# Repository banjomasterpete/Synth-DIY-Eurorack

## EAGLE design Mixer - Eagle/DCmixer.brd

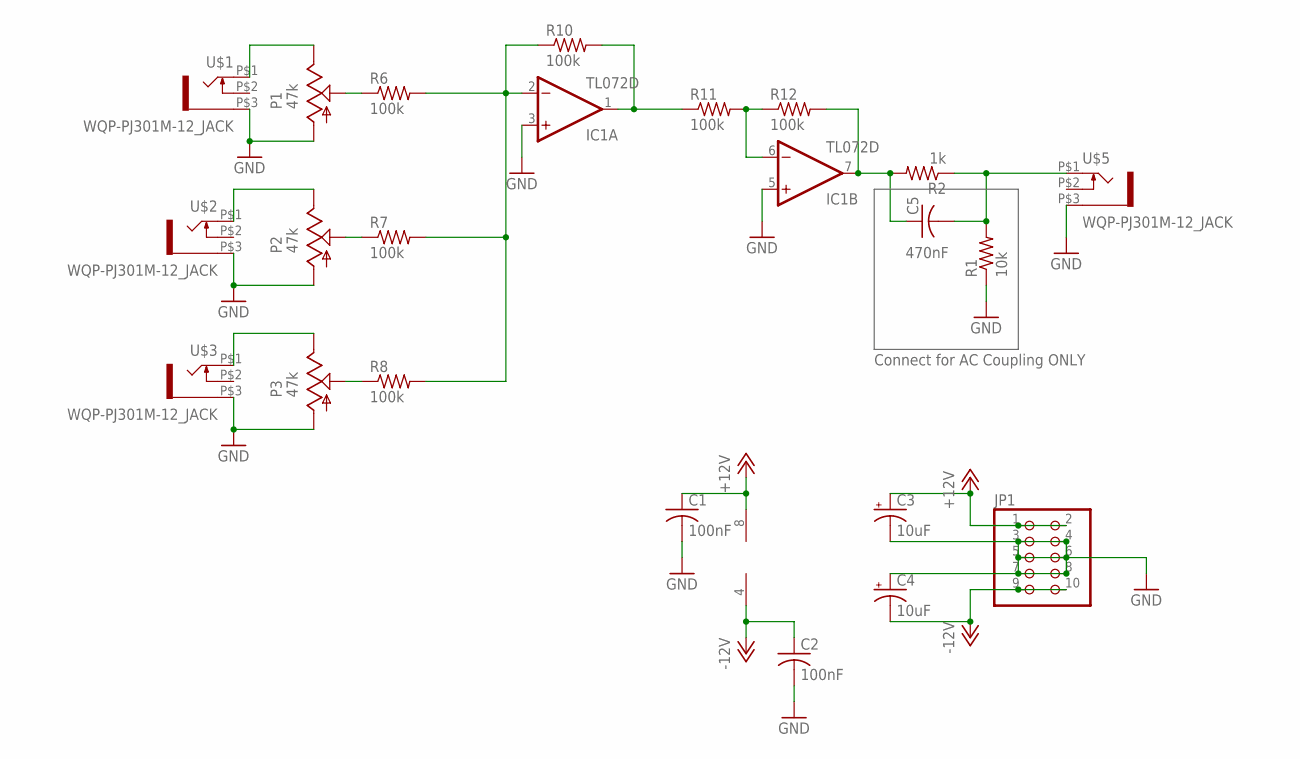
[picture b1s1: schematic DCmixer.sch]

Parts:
C1, C2: 100nF; C0603K
C3, C4: 10uF; E2-5
C5: 470nF; C0603K
IC1: TL072D; SO08
JP1: PINHD-2X5; 2X05
P1, P2, P3: 47k; EVUF
R1: 10k; R0603
R2: 1k; R0603
R6, R7, R8, R10, R11, R12: 100k; R0603
U$1, U$2, U$3, U$5: WQP-PJ301M-12_JACK

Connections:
+12V: C1.1, C3.+, IC1.8 (V+), JP1.1, JP1.2
-12V: C2.1, C4.-, IC1.4 (V-), JP1.9, JP1.10
GND: C1.2, C2.2, C3.-, C4.+, IC1.3 (+IN), IC1.5 (+IN), JP1.3, JP1.4, JP1.5, JP1.6, JP1.7, JP1.8, P1.1 (A), P2.1 (A), P3.1 (A), R1.1, U$1.P$3 (1), U$2.P$3 (1), U$3.P$3 (1), U$5.P$3 (1)
unnamed: P1.3 (E), U$1.P$1 (2)
unnamed: P2.3 (E), U$2.P$1 (2)
unnamed: P3.3 (E), U$3.P$1 (2)
unnamed: P3.2 (S), R8.1
unnamed: P2.2 (S), R7.1
unnamed: P1.2 (S), R6.1
unnamed: IC1.2 (-IN), R6.2, R7.2, R8.2, R10.1
unnamed: C5.2, R1.2, R2.1, U$5.P$1 (2)
unnamed: IC1.1 (OUT), R10.2, R11.1
unnamed: IC1.6 (-IN), R11.2, R12.1
unnamed: C5.1, IC1.7 (OUT), R2.2, R12.2

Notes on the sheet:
Connect for AC Coupling ONLY

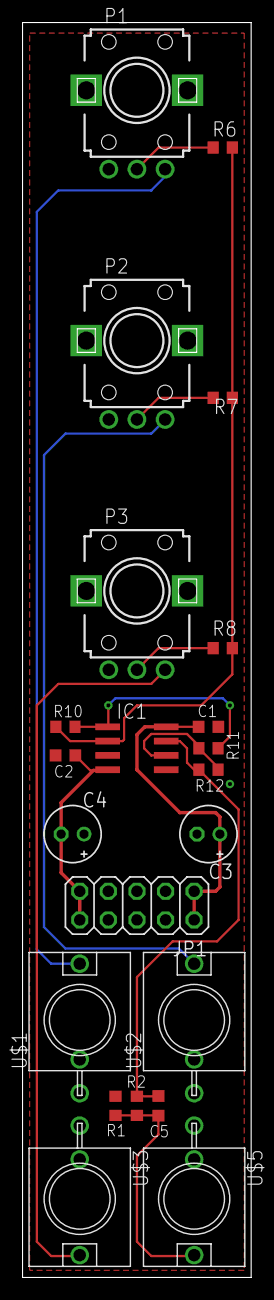
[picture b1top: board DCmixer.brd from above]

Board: 2 copper layers, 20.3 x 111.4 mm, 22 parts (0 on the bottom side), 14 nets.

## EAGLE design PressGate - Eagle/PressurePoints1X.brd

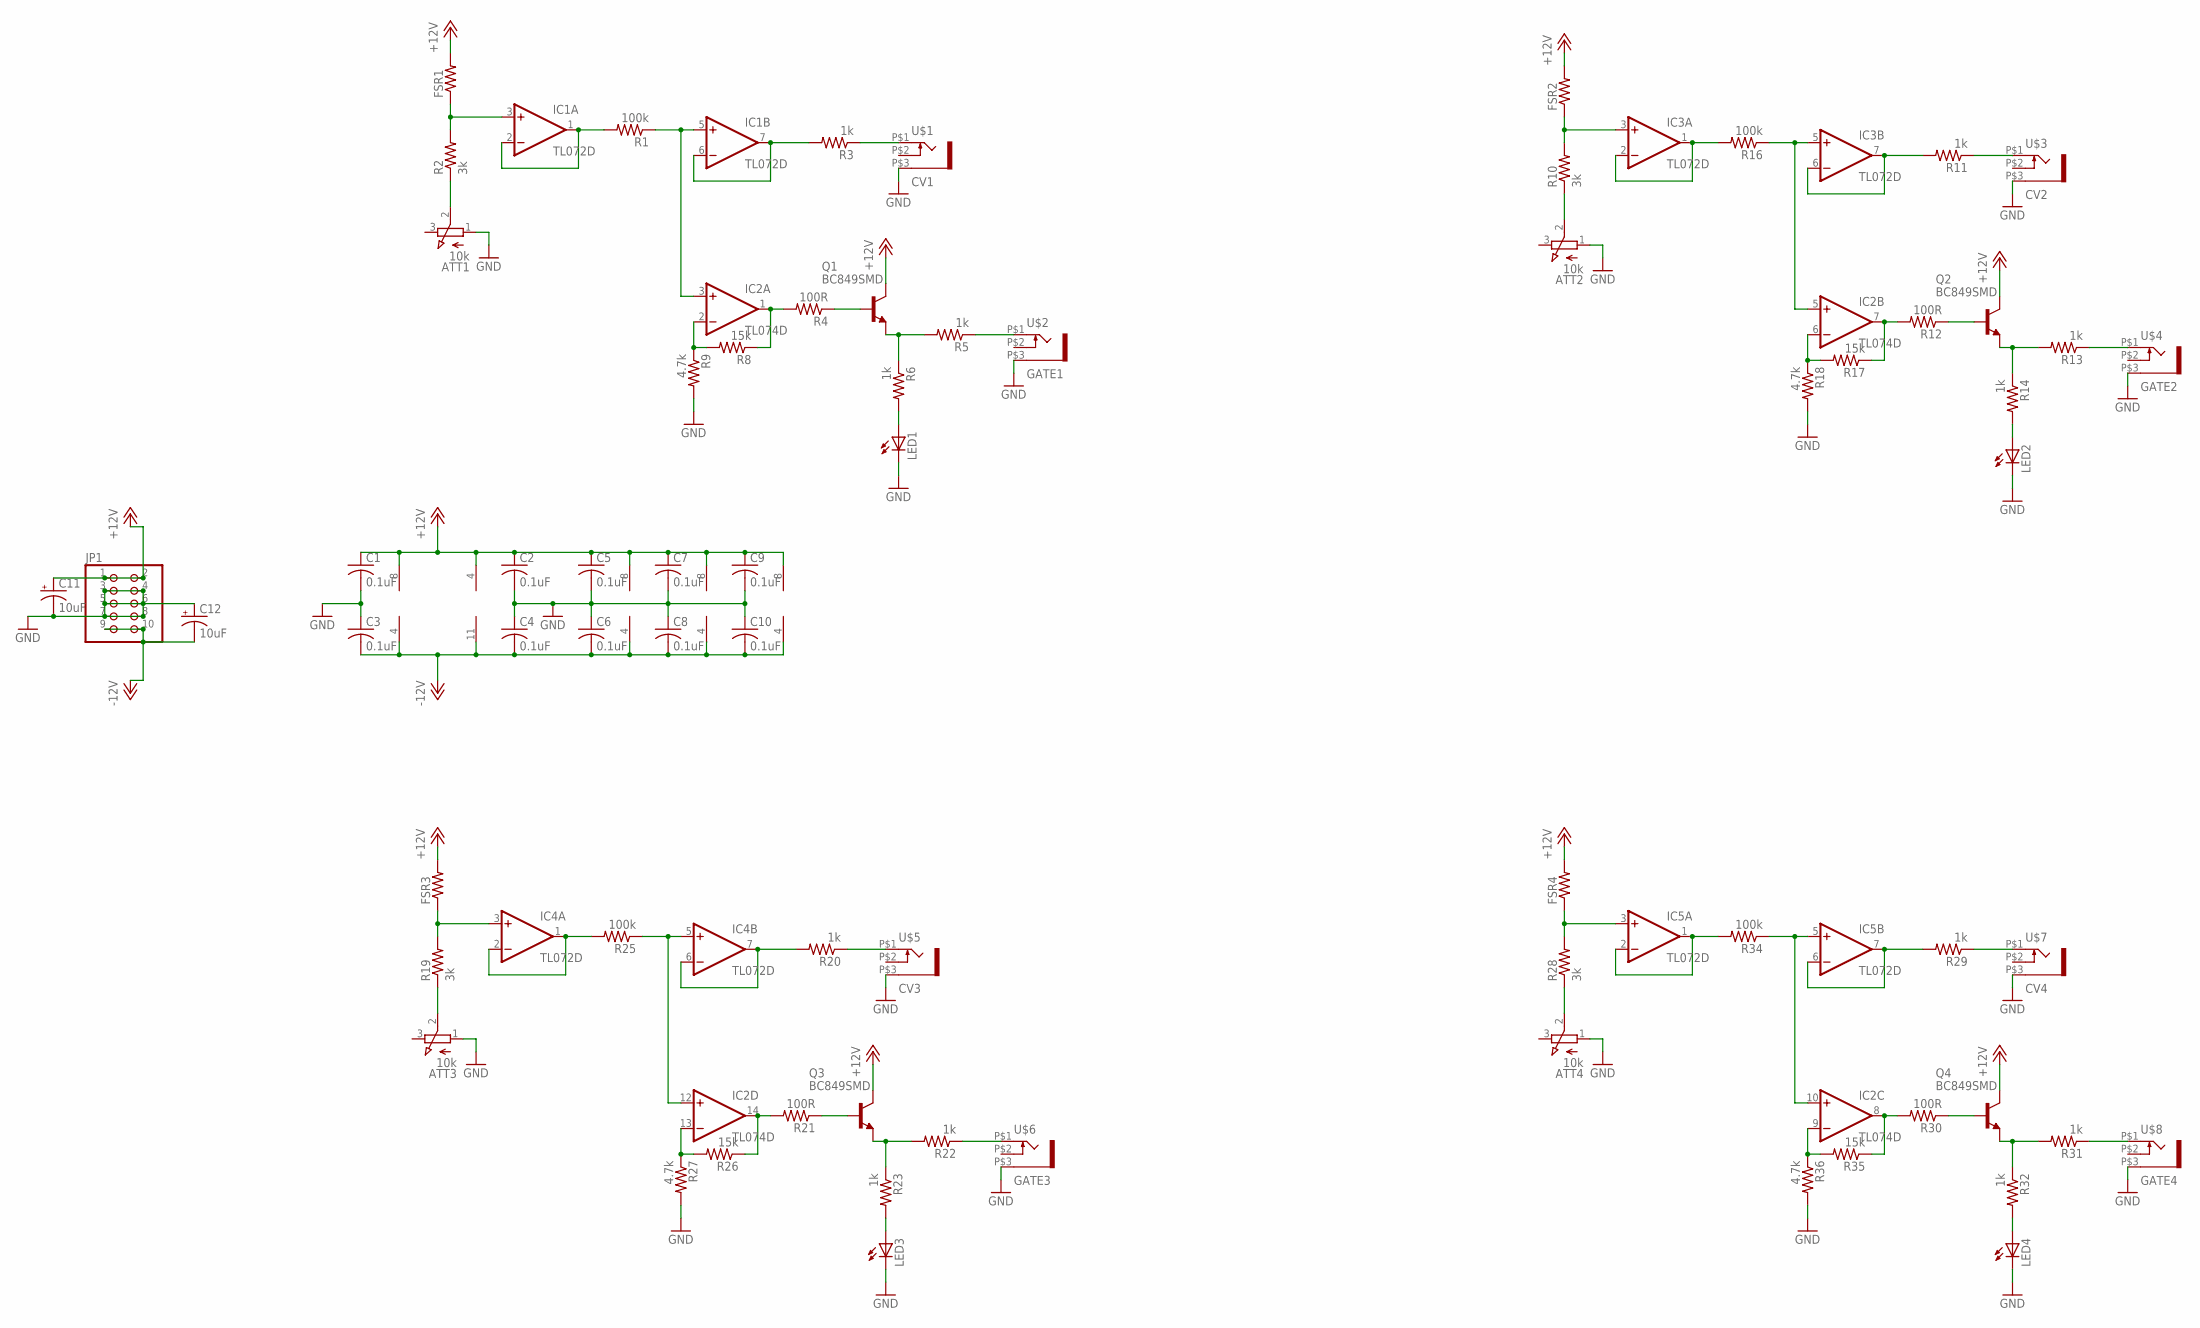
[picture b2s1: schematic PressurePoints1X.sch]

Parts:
ATT1, ATT2, ATT3, ATT4: 10k; EVUFXJ
C1, C2, C3, C4, C5, C6, C7, C8, C9, C10: 0.1uF; C0603
C11, C12: 10uF; E2-5
FSR1, FSR2, FSR3, FSR4: R-US_0207/2V; 0207/2V
IC1, IC3, IC4, IC5: TL072D; SO08
IC2: TL074D; SO14
JP1: PINHD-2X5; 2X05
LED1, LED2, LED3, LED4: LED3MM
Q1, Q2, Q3, Q4: BC849SMD; SOT23-BEC
R1, R16, R25, R34: 100k; R0603
R2, R10, R19, R28: 3k; R0603
R3, R5, R6, R11, R13, R14, R20, R22, R23, R29, R31, R32: 1k; R0603
R4, R12, R21, R30: 100R; R0603
R8, R17, R26, R35: 15k; R0603
R9, R18, R27, R36: 4.7k; R0603
U$1: CV1; WQP-PJ301M-12_JACK
U$2: GATE1; WQP-PJ301M-12_JACK
U$3: CV2; WQP-PJ301M-12_JACK
U$4: GATE2; WQP-PJ301M-12_JACK
U$5: CV3; WQP-PJ301M-12_JACK
U$6: GATE3; WQP-PJ301M-12_JACK
U$7: CV4; WQP-PJ301M-12_JACK
U$8: GATE4; WQP-PJ301M-12_JACK

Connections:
+12V: C1.1, C2.1, C5.1, C7.1, C9.1, C11.+, FSR1.2, FSR2.2, FSR3.2, FSR4.2, IC1.8 (V+), IC2.4 (V+), IC3.8 (V+), IC4.8 (V+), IC5.8 (V+), JP1.1, JP1.2, Q1.C, Q2.C, Q3.C, Q4.C
-12V: C3.2, C4.2, C6.2, C8.2, C10.2, C12.-, IC1.4 (V-), IC2.11 (V-), IC3.4 (V-), IC4.4 (V-), IC5.4 (V-), JP1.9, JP1.10
GND: ATT1.1 (A), ATT2.1 (A), ATT3.1 (A), ATT4.1 (A), C1.2, C2.2, C3.1, C4.1, C5.2, C6.1, C7.2, C8.1, C9.2, C10.1, C11.-, C12.+, JP1.3, JP1.4, JP1.5, JP1.6, JP1.7, JP1.8, LED1.K (C), LED2.K (C), LED3.K (C), LED4.K (C), R9.2, R18.2, R27.2, R36.2, U$1.P$3 (1), U$2.P$3 (1), U$3.P$3 (1), U$4.P$3 (1), U$5.P$3 (1), U$6.P$3 (1), U$7.P$3 (1), U$8.P$3 (1)
unnamed: FSR1.1, IC1.3 (+IN), R2.2
unnamed: ATT1.2 (S), R2.1
unnamed: IC1.5 (+IN), IC2.3 (+IN), R1.1
unnamed: IC1.6 (-IN), IC1.7 (OUT), R3.2
unnamed: R3.1, U$1.P$1 (2)
unnamed: Q1.E, R5.2, R6.1
unnamed: IC2.1 (OUT), R4.2, R8.1
unnamed: Q1.B, R4.1
unnamed: LED1.A, R6.2
unnamed: R5.1, U$2.P$1 (2)
unnamed: IC1.1 (OUT), IC1.2 (-IN), R1.2
unnamed: IC2.2 (-IN), R8.2, R9.1
unnamed: FSR2.1, IC3.3 (+IN), R10.2
unnamed: IC2.5 (+IN), IC3.5 (+IN), R16.1
unnamed: IC3.6 (-IN), IC3.7 (OUT), R11.2
unnamed: R11.1, U$3.P$1 (2)
unnamed: IC2.7 (OUT), R12.2, R17.1
unnamed: Q2.B, R12.1
unnamed: LED2.A, R14.2
unnamed: Q2.E, R13.2, R14.1
unnamed: R13.1, U$4.P$1 (2)
unnamed: ATT2.2 (S), R10.1
unnamed: IC3.1 (OUT), IC3.2 (-IN), R16.2
unnamed: IC2.6 (-IN), R17.2, R18.1
unnamed: FSR3.1, IC4.3 (+IN), R19.2
unnamed: IC2.12 (+IN), IC4.5 (+IN), R25.1
unnamed: IC4.6 (-IN), IC4.7 (OUT), R20.2
unnamed: R20.1, U$5.P$1 (2)
unnamed: IC2.14 (OUT), R21.2, R26.1
unnamed: Q3.B, R21.1
unnamed: LED3.A, R23.2
unnamed: Q3.E, R22.2, R23.1
unnamed: R22.1, U$6.P$1 (2)
unnamed: ATT3.2 (S), R19.1
unnamed: IC4.1 (OUT), IC4.2 (-IN), R25.2
unnamed: IC2.13 (-IN), R26.2, R27.1
unnamed: FSR4.1, IC5.3 (+IN), R28.2
unnamed: IC2.10 (+IN), IC5.5 (+IN), R34.1
unnamed: IC5.6 (-IN), IC5.7 (OUT), R29.2
unnamed: R29.1, U$7.P$1 (2)
unnamed: IC2.8 (OUT), R30.2, R35.1
unnamed: Q4.B, R30.1
unnamed: LED4.A, R32.2
unnamed: Q4.E, R31.2, R32.1
unnamed: R31.1, U$8.P$1 (2)
unnamed: ATT4.2 (S), R28.1
unnamed: IC5.1 (OUT), IC5.2 (-IN), R34.2
unnamed: IC2.9 (-IN), R35.2, R36.1

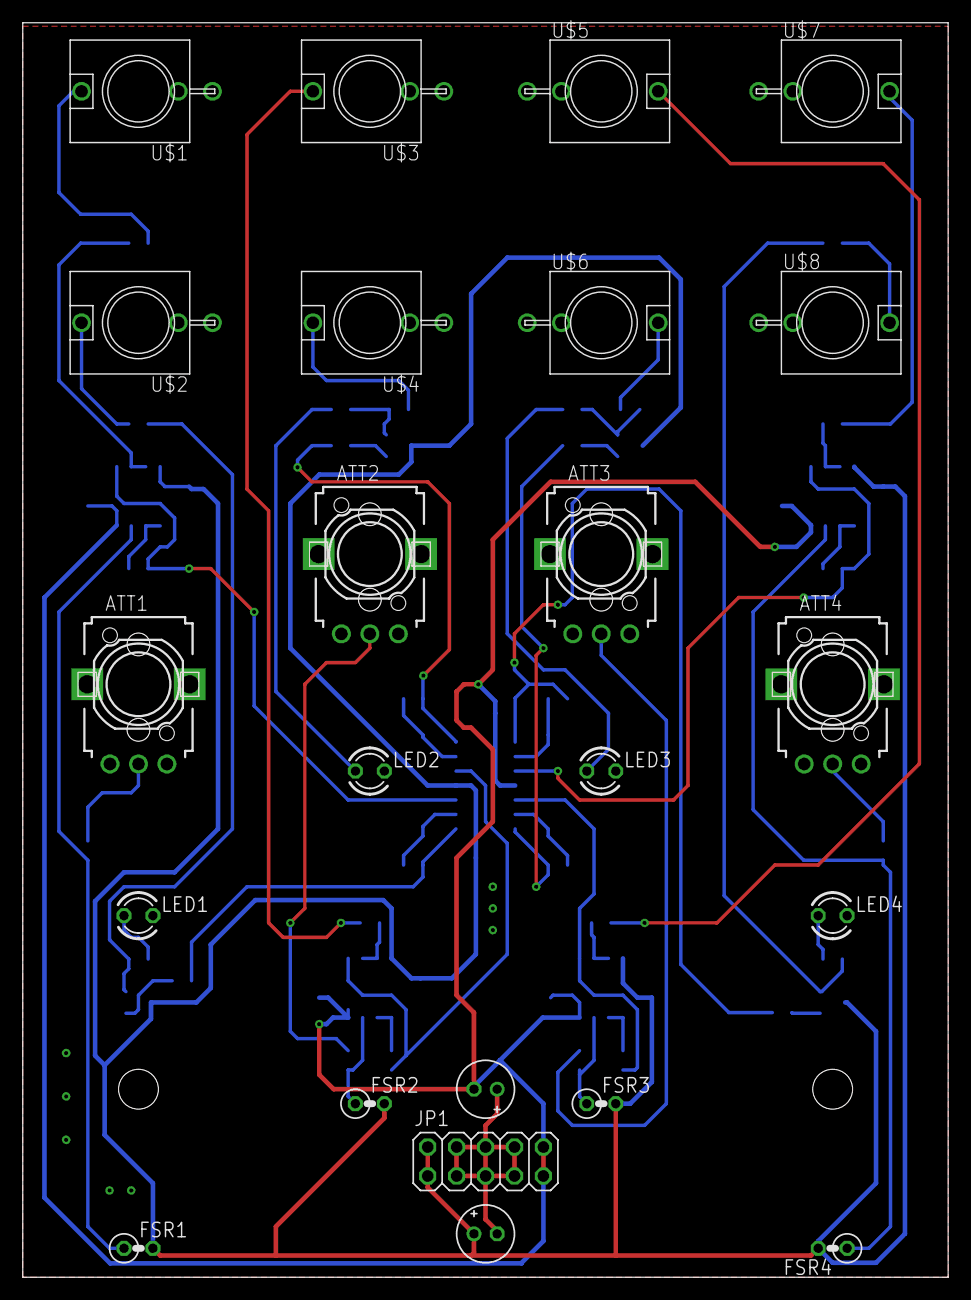
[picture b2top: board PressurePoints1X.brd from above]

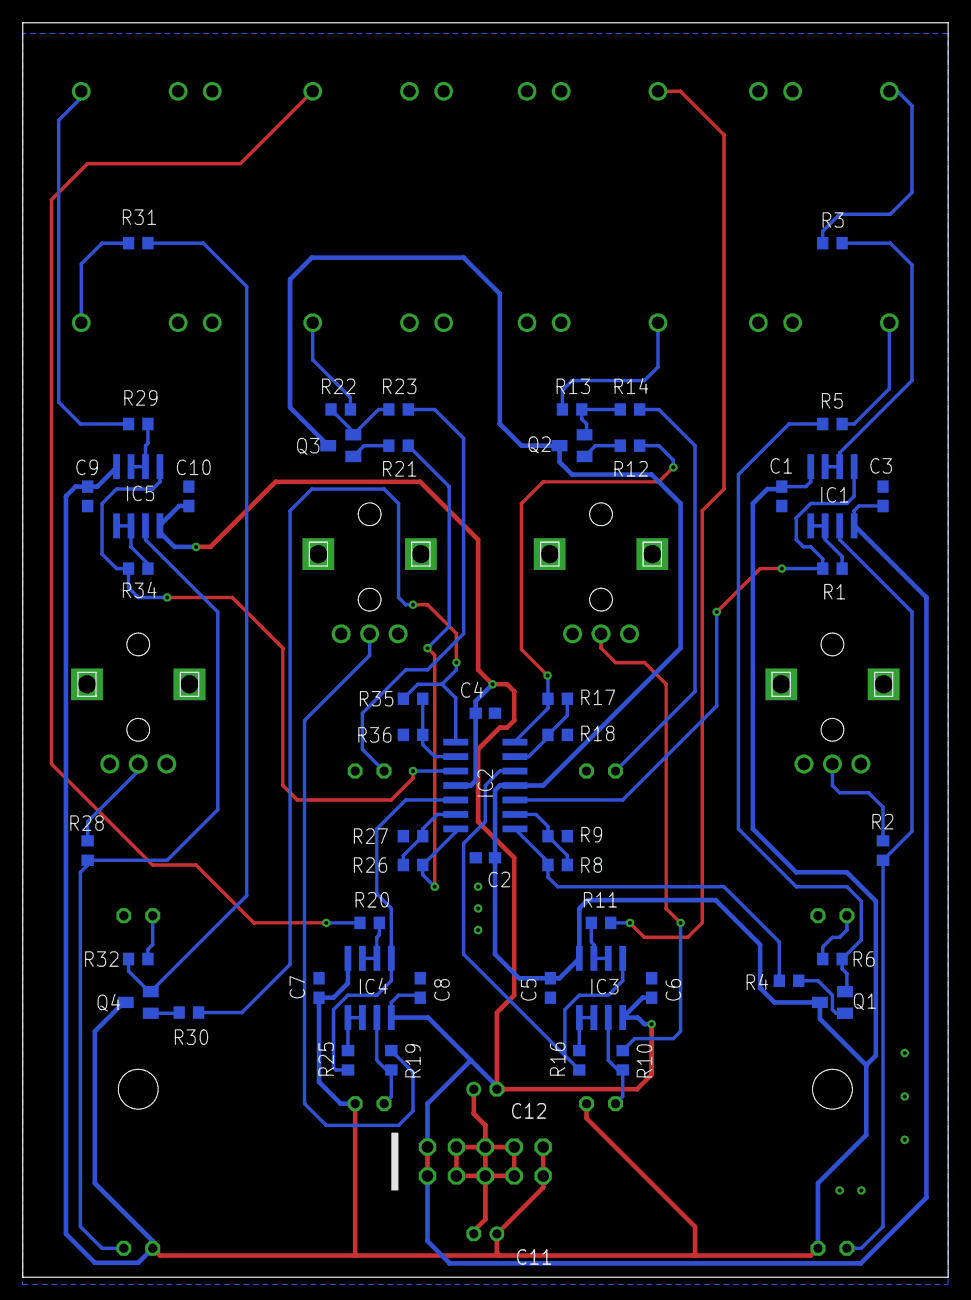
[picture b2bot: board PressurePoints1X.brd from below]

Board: 2 copper layers, 81.3 x 110.2 mm, 74 parts (51 on the bottom side), 51 nets.

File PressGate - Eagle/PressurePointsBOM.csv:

"Qty";"Value";"Device";"Package";"Parts";"Description";"SPICEPREFIX";
"4";"";"LED3MM";"LED3MM";"LED1, LED2, LED3, LED4";"LED";"";
"1";"";"PINHD-2X5";"2X05";"JP1";"PIN HEADER";"";
"4";"";"R-US_0207/2V";"0207/2V";"FSR1, FSR2, FSR3, FSR4";"RESISTOR, American symbol";"R";
"10";"0.1uF";"C-USC0603";"C0603";"C1, C2, C3, C4, C5, C6, C7, C8, C9, C10";"CAPACITOR, American symbol";"C";
"4";"100R";"R-US_R0603";"R0603";"R4, R12, R21, R30";"RESISTOR, American symbol";"R";
"4";"100k";"R-US_R0603";"R0603";"R1, R16, R25, R34";"RESISTOR, American symbol";"R";
"4";"10k";"EVUF2J";"EVUFXJ";"ATT1, ATT2, ATT3, ATT4";"9 mm Square Rotary Potentiometers";"";
"2";"10uF";"CPOL-USE2-5";"E2-5";"C11, C12";"POLARIZED CAPACITOR, American symbol";"C";
"4";"15k";"R-US_R0603";"R0603";"R8, R17, R26, R35";"RESISTOR, American symbol";"R";
"12";"1k";"R-US_R0603";"R0603";"R3, R5, R6, R11, R13, R14, R20, R22, R23, R29, R31, R32";"RESISTOR, American symbol";"R";
"4";"3k";"R-US_R0603";"R0603";"R2, R10, R19, R28";"RESISTOR, American symbol";"R";
"4";"4.7k";"R-US_R0603";"R0603";"R9, R18, R27, R36";"RESISTOR, American symbol";"R";
"4";"BC849SMD";"BC849SMD";"SOT23-BEC";"Q1, Q2, Q3, Q4";"NPN Transistor";"";
"1";"CV1";"WQP-PJ301M-12_JACK";"WQP-PJ301M-12_JACK";"U$1";"";"";
"1";"CV2";"WQP-PJ301M-12_JACK";"WQP-PJ301M-12_JACK";"U$3";"";"";
"1";"CV3";"WQP-PJ301M-12_JACK";"WQP-PJ301M-12_JACK";"U$5";"";"";
"1";"CV4";"WQP-PJ301M-12_JACK";"WQP-PJ301M-12_JACK";"U$7";"";"";
"1";"GATE1";"WQP-PJ301M-12_JACK";"WQP-PJ301M-12_JACK";"U$2";"";"";
"1";"GATE2";"WQP-PJ301M-12_JACK";"WQP-PJ301M-12_JACK";"U$4";"";"";
"1";"GATE3";"WQP-PJ301M-12_JACK";"WQP-PJ301M-12_JACK";"U$6";"";"";
"1";"GATE4";"WQP-PJ301M-12_JACK";"WQP-PJ301M-12_JACK";"U$8";"";"";
"4";"TL072D";"TL072D";"SO08";"IC1, IC3, IC4, IC5";"OP AMP";"";
"1";"TL074D";"TL074D";"SO14";"IC2";"OP AMP";"";

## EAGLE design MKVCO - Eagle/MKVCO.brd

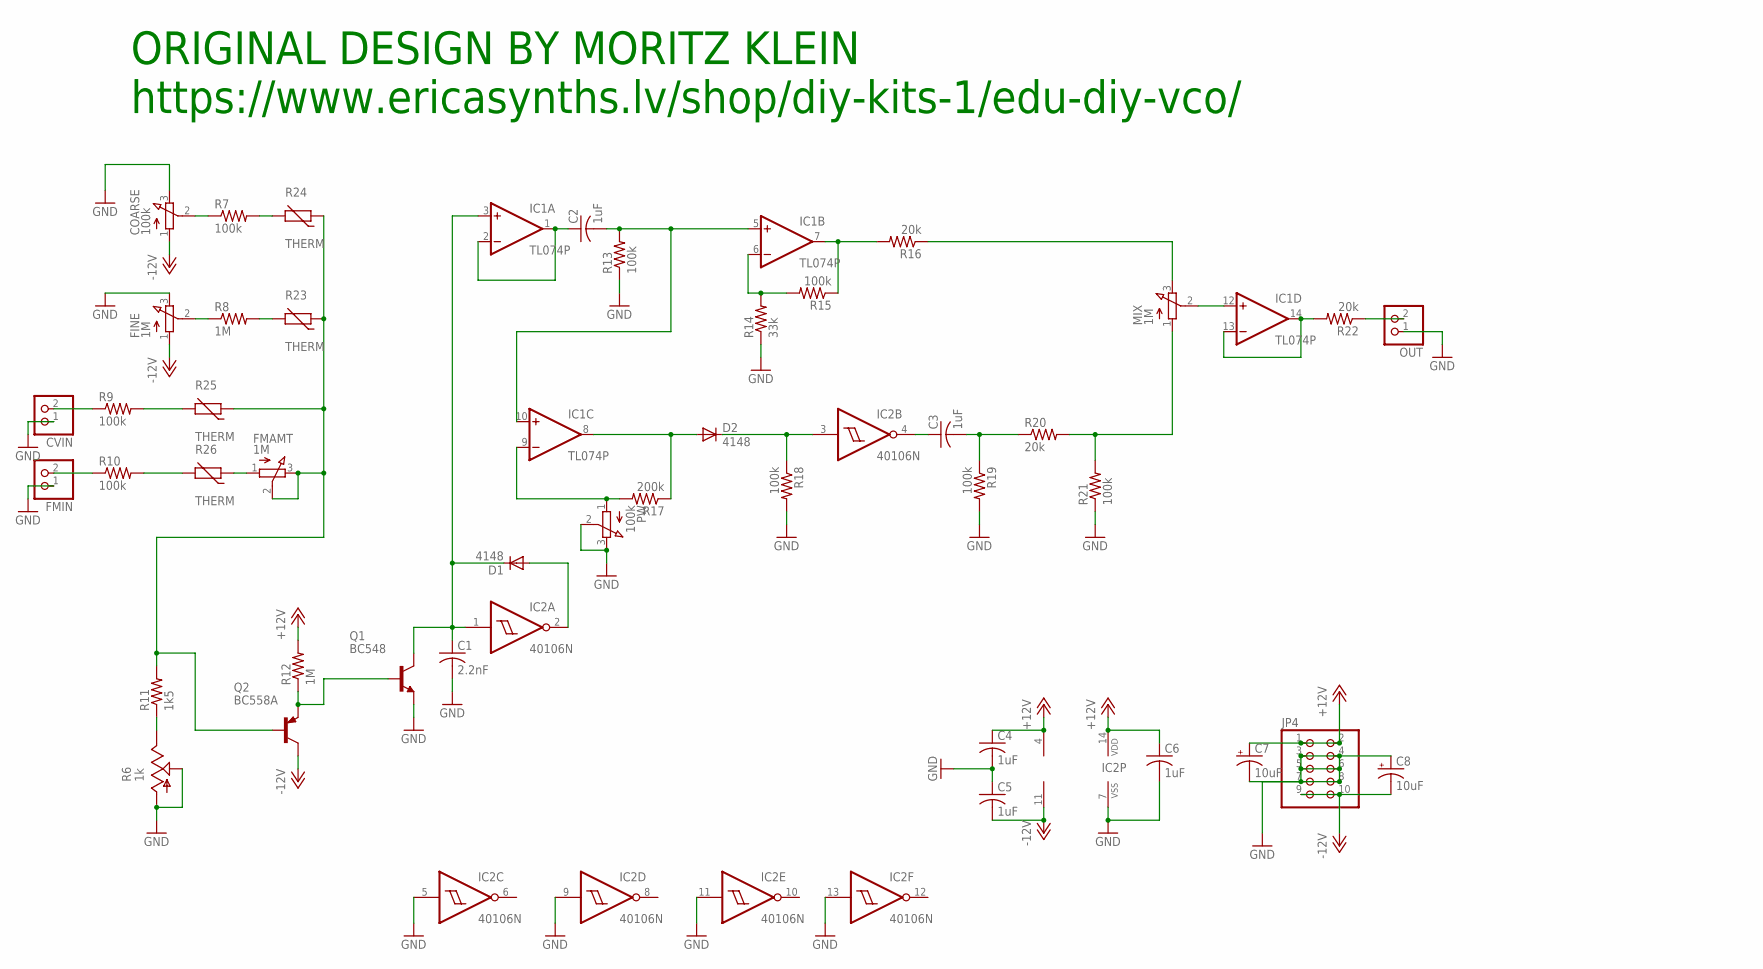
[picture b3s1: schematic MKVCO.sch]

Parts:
C1: 2.2nF; C050-025X075
C2, C3: 1uF; C050-025X075
C4, C5, C6: 1uF; C050-024X044
C7, C8: 10uF; E1,8-4
COARSE: 100k; 3RP/1610N
CVIN: PINHD-1X2; 1X02
D1, D2: 4148; DO35-7
FINE: 1M; 3RP/1610N
FMAMT: 1M; 3RP/1610N
FMIN: PINHD-1X2; 1X02
IC1: TL074P; DIL14
IC2: 40106N; DIL14
JP4: PINHD-2X5; 2X05
MIX: 1M; 3RP/1610N
OUT: PINHD-1X2; 1X02
PW: 100k; 3RP/1610N
Q1: BC548; TO92-EBC
Q2: BC558A; TO92-EBC
R6: 1k; B64Y
R7, R9, R10, R13, R15, R18, R19, R21: 100k; 0207/10
R8, R12: 1M; 0207/10
R11: 1k5; 0207/10
R14: 33k; 0207/10
R16, R20, R22: 20k; 0207/10
R17: 200k; 0207/10
R23, R24, R25, R26: THERM; RS-2,5

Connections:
+12V: C4.1, C6.1, C7.+, IC1.4 (V+), IC2.14 (VDD), JP4.1, JP4.2, R12.2
-12V: C5.2, C8.-, COARSE.1 (A), FINE.1 (A), IC1.11 (V-), JP4.9, JP4.10, Q2.C
GND: C1.2, C4.2, C5.1, C6.2, C7.-, C8.+, COARSE.3 (E), CVIN.1, FINE.3 (E), FMIN.1, IC2.5 (I), IC2.7 (VSS), IC2.9 (I), IC2.11 (I), IC2.13 (I), JP4.3, JP4.4, JP4.5, JP4.6, JP4.7, JP4.8, OUT.1, PW.2 (S), PW.3 (E), Q1.E, R6.A, R6.S, R13.1, R14.1, R18.2, R19.2, R21.1
unnamed: COARSE.2 (S), R7.1
unnamed: FINE.2 (S), R8.1
unnamed: CVIN.2, R9.1
unnamed: R9.2, R25.2
unnamed: FMAMT.2 (S), FMAMT.3 (E), Q2.B, R11.2, R23.1, R24.1, R25.1
unnamed: C1.1, D1.C, IC1.3 (+IN), IC2.1 (I), Q1.C
unnamed: D1.A, IC2.2 (O)
unnamed: R6.E, R11.1
unnamed: IC1.12 (+IN), MIX.2 (S)
unnamed: IC1.13 (-IN), IC1.14 (OUT), R22.2
unnamed: Q1.B, Q2.E, R12.1
unnamed: C2.1, IC1.1 (OUT), IC1.2 (-IN)
unnamed: C2.2, IC1.5 (+IN), IC1.10 (+IN), R13.2
unnamed: OUT.2, R22.1
unnamed: IC1.9 (-IN), PW.1 (A), R17.2
unnamed: D2.A, IC1.8 (OUT), R17.1
unnamed: R7.2, R24.2
unnamed: MIX.3 (E), R16.1
unnamed: D2.C, IC2.3 (I), R18.1
unnamed: C3.1, IC2.4 (O)
unnamed: C3.2, R19.1, R20.1
unnamed: IC1.6 (-IN), R14.2, R15.2
unnamed: IC1.7 (OUT), R15.1, R16.2
unnamed: MIX.1 (A), R20.2, R21.2
unnamed: R8.2, R23.2
unnamed: R10.2, R26.2
unnamed: FMIN.2, R10.1
unnamed: FMAMT.1 (A), R26.1

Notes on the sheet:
ORIGINAL DESIGN BY MORITZ KLEIN https://www.ericasynths.lv/shop/diy-kits-1/edu-diy-vco/

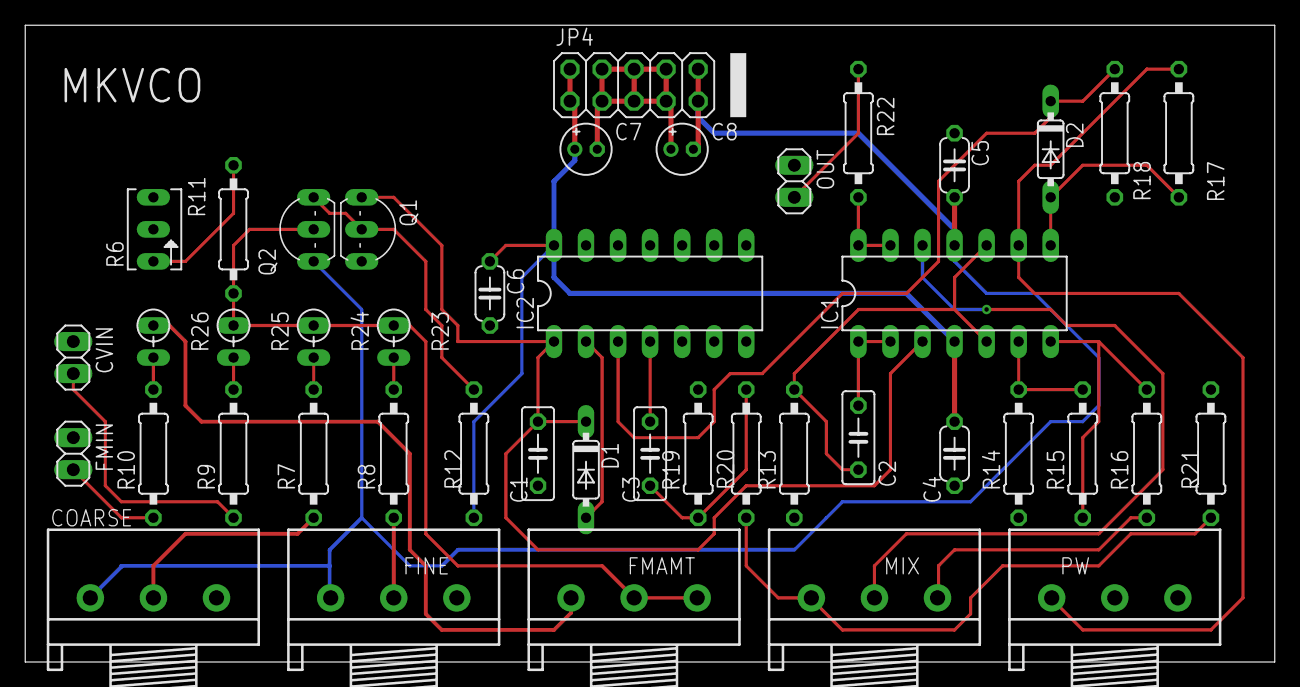
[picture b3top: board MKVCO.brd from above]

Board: 2 copper layers, 99.0 x 50.5 mm, 44 parts (0 on the bottom side), 31 nets.

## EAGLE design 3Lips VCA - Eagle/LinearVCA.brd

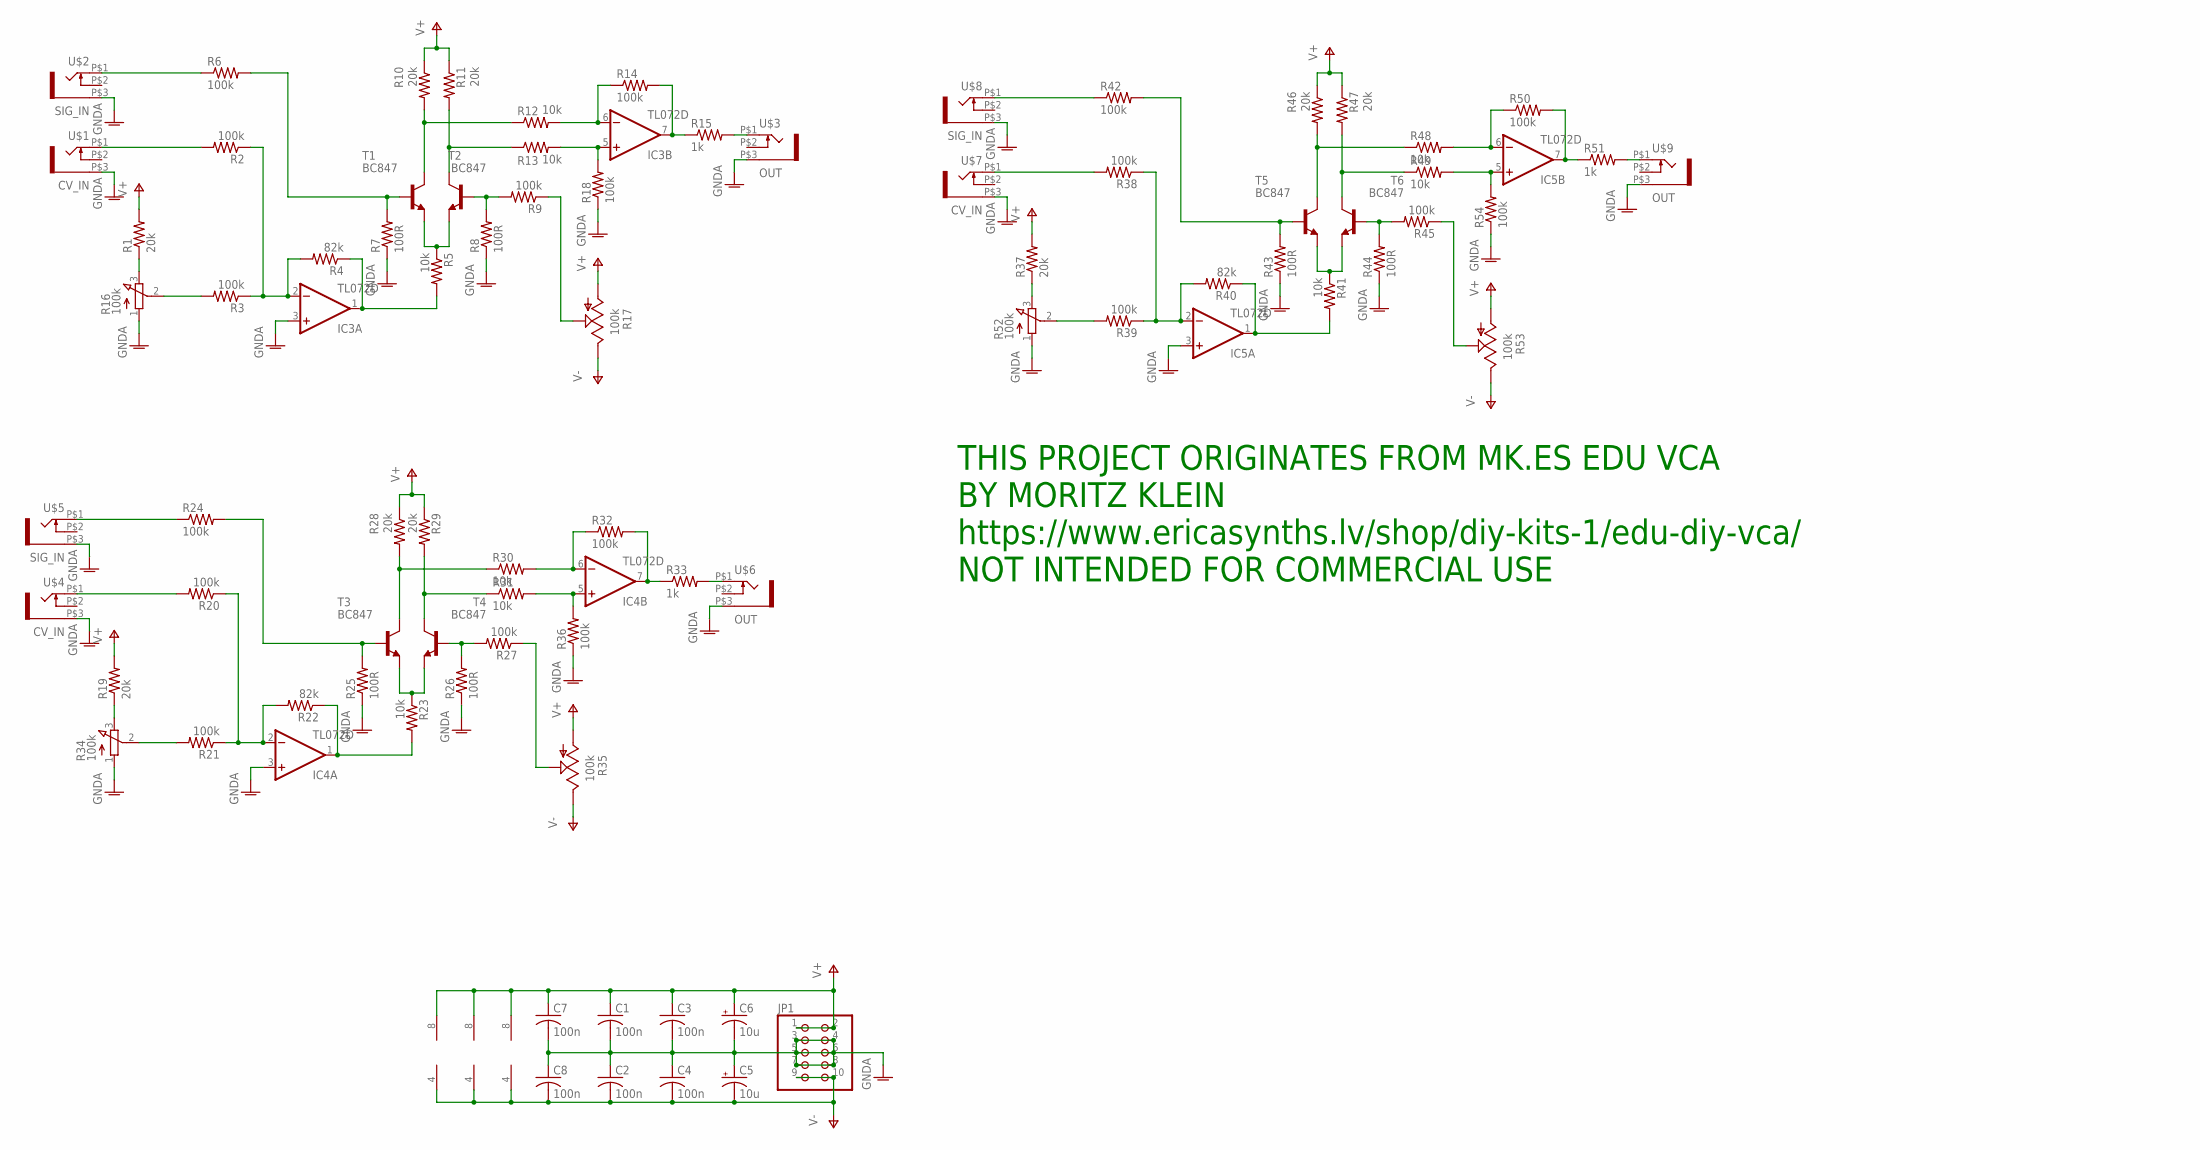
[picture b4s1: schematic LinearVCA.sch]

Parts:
C1, C2, C3, C4, C7, C8: 100n; C0603K
C5, C6: 10u; E2-5
IC3, IC4, IC5: TL072D; SO08
JP1: PINHD-2X5; 2X05
R1, R10, R11, R19, R28, R29, R37, R46, R47: 20k; R0603
R2, R3, R6, R9, R14, R18, R20, R21, R24, R27, R32, R36, R38, R39, R42, R45, R50, R54: 100k; R0603
R4, R22, R40: 82k; R0603
R5, R12, R13, R23, R30, R31, R41, R48, R49: 10k; R0603
R7, R8, R25, R26, R43, R44: 100R; R0603
R15, R33, R51: 1k; R0603
R16, R34, R52: 100k; EVUFXK
R17, R35, R53: 100k; RJ9W
T1, T2, T3, T4, T5, T6: BC847; SOT23
U$1, U$4, U$7: CV_IN; WQP-PJ301M-12_JACK
U$2, U$5, U$8: SIG_IN; WQP-PJ301M-12_JACK
U$3, U$6, U$9: OUT; WQP-PJ301M-12_JACK

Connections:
GNDA: C1.2, C2.1, C3.2, C4.1, C5.+, C6.-, C7.2, C8.1, IC3.3 (+IN), IC4.3 (+IN), IC5.3 (+IN), JP1.3, JP1.4, JP1.5, JP1.6, JP1.7, JP1.8, R7.1, R8.1, R16.1 (A), R18.1, R25.1, R26.1, R34.1 (A), R36.1, R43.1, R44.1, R52.1 (A), R54.1, U$1.P$3 (1), U$2.P$3 (1), U$3.P$3 (1), U$4.P$3 (1), U$5.P$3 (1), U$6.P$3 (1), U$7.P$3 (1), U$8.P$3 (1), U$9.P$3 (1)
unnamed: IC3.2 (-IN), R2.1, R3.1, R4.2
unnamed: R1.1, R16.3 (E)
unnamed: R3.2, R16.2 (S)
unnamed: R2.2, U$1.P$1 (2)
unnamed: IC3.1 (OUT), R4.1, R5.2
unnamed: R5.1, T1.2 (E), T2.2 (E)
unnamed: R6.2, R7.2, T1.1 (B)
unnamed: R6.1, U$2.P$1 (2)
unnamed: R8.2, R9.2, T2.1 (B)
unnamed: R9.1, R17.S
unnamed: R10.2, R12.1, T1.3 (C)
unnamed: R11.2, R13.1, T2.3 (C)
unnamed: IC3.6 (-IN), R12.2, R14.1
unnamed: IC3.5 (+IN), R13.2, R18.2
unnamed: R15.2, U$3.P$1 (2)
unnamed: IC3.7 (OUT), R14.2, R15.1
unnamed: IC4.2 (-IN), R20.1, R21.1, R22.2
unnamed: R19.1, R34.3 (E)
unnamed: R21.2, R34.2 (S)
unnamed: IC4.1 (OUT), R22.1, R23.2
unnamed: R23.1, T3.2 (E), T4.2 (E)
unnamed: R20.2, U$4.P$1 (2)
unnamed: R24.2, R25.2, T3.1 (B)
unnamed: R24.1, U$5.P$1 (2)
unnamed: R26.2, R27.2, T4.1 (B)
unnamed: R27.1, R35.S
unnamed: R28.2, R30.1, T3.3 (C)
unnamed: R29.2, R31.1, T4.3 (C)
unnamed: IC4.6 (-IN), R30.2, R32.1
unnamed: IC4.5 (+IN), R31.2, R36.2
unnamed: IC4.7 (OUT), R32.2, R33.1
unnamed: R33.2, U$6.P$1 (2)
unnamed: IC5.2 (-IN), R38.1, R39.1, R40.2
unnamed: R37.1, R52.3 (E)
unnamed: R39.2, R52.2 (S)
unnamed: IC5.1 (OUT), R40.1, R41.2
unnamed: R41.1, T5.2 (E), T6.2 (E)
unnamed: R38.2, U$7.P$1 (2)
unnamed: R42.2, R43.2, T5.1 (B)
unnamed: R42.1, U$8.P$1 (2)
unnamed: R44.2, R45.2, T6.1 (B)
unnamed: R45.1, R53.S
unnamed: R46.2, R48.1, T5.3 (C)
unnamed: R47.2, R49.1, T6.3 (C)
unnamed: IC5.6 (-IN), R48.2, R50.1
unnamed: IC5.5 (+IN), R49.2, R54.2
unnamed: IC5.7 (OUT), R50.2, R51.1
unnamed: R51.2, U$9.P$1 (2)
V+: C1.1, C3.1, C6.+, C7.1, IC3.8 (V+), IC4.8 (V+), IC5.8 (V+), JP1.1, JP1.2, R1.2, R10.1, R11.1, R17.A, R19.2, R28.1, R29.1, R35.A, R37.2, R46.1, R47.1, R53.A
V-: C2.2, C4.2, C5.-, C8.2, IC3.4 (V-), IC4.4 (V-), IC5.4 (V-), JP1.9, JP1.10, R17.E, R35.E, R53.E

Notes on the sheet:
THIS PROJECT ORIGINATES FROM MK.ES EDU VCA BY MORITZ KLEIN https://www.ericasynths.lv/shop/diy-kits-1/edu-diy-vca/ NOT INTENDED FOR COMMERCIAL USE

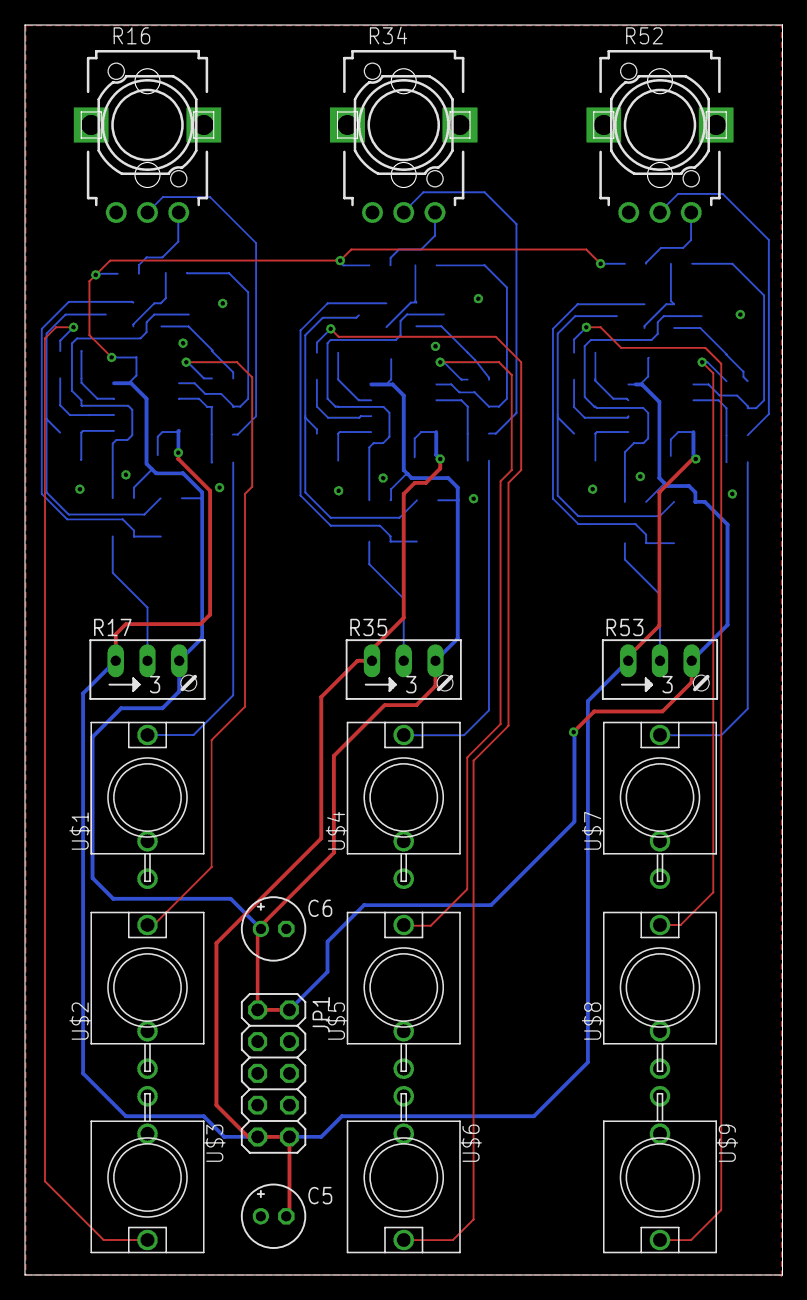
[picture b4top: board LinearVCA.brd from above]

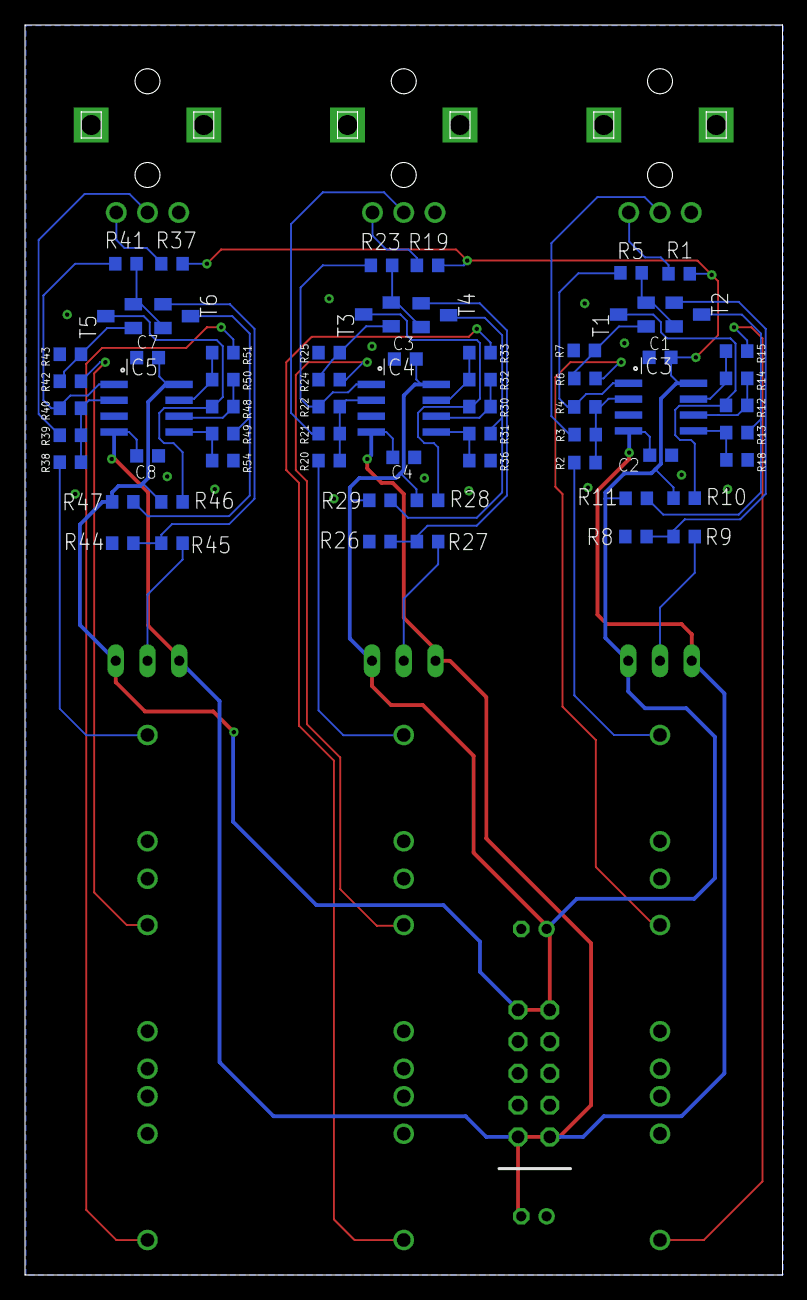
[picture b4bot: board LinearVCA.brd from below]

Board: 2 copper layers, 60.6 x 100.0 mm, 81 parts (63 on the bottom side), 51 nets.
